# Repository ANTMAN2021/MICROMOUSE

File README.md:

# MICROMOUSE
As a Team Robotics projects, this is a stm32 based micromouse.
There are two pcbs, one based on stm32f103c8t6 and other on stm32f405rgt6.
The assembled bot is on stm32f103 bluepill.
Motor driver used is DRV8833 and sensors are IR sensors.
N20 motors with encoders are used.
Basic running code is given above, shortest path algorithm is in progress.

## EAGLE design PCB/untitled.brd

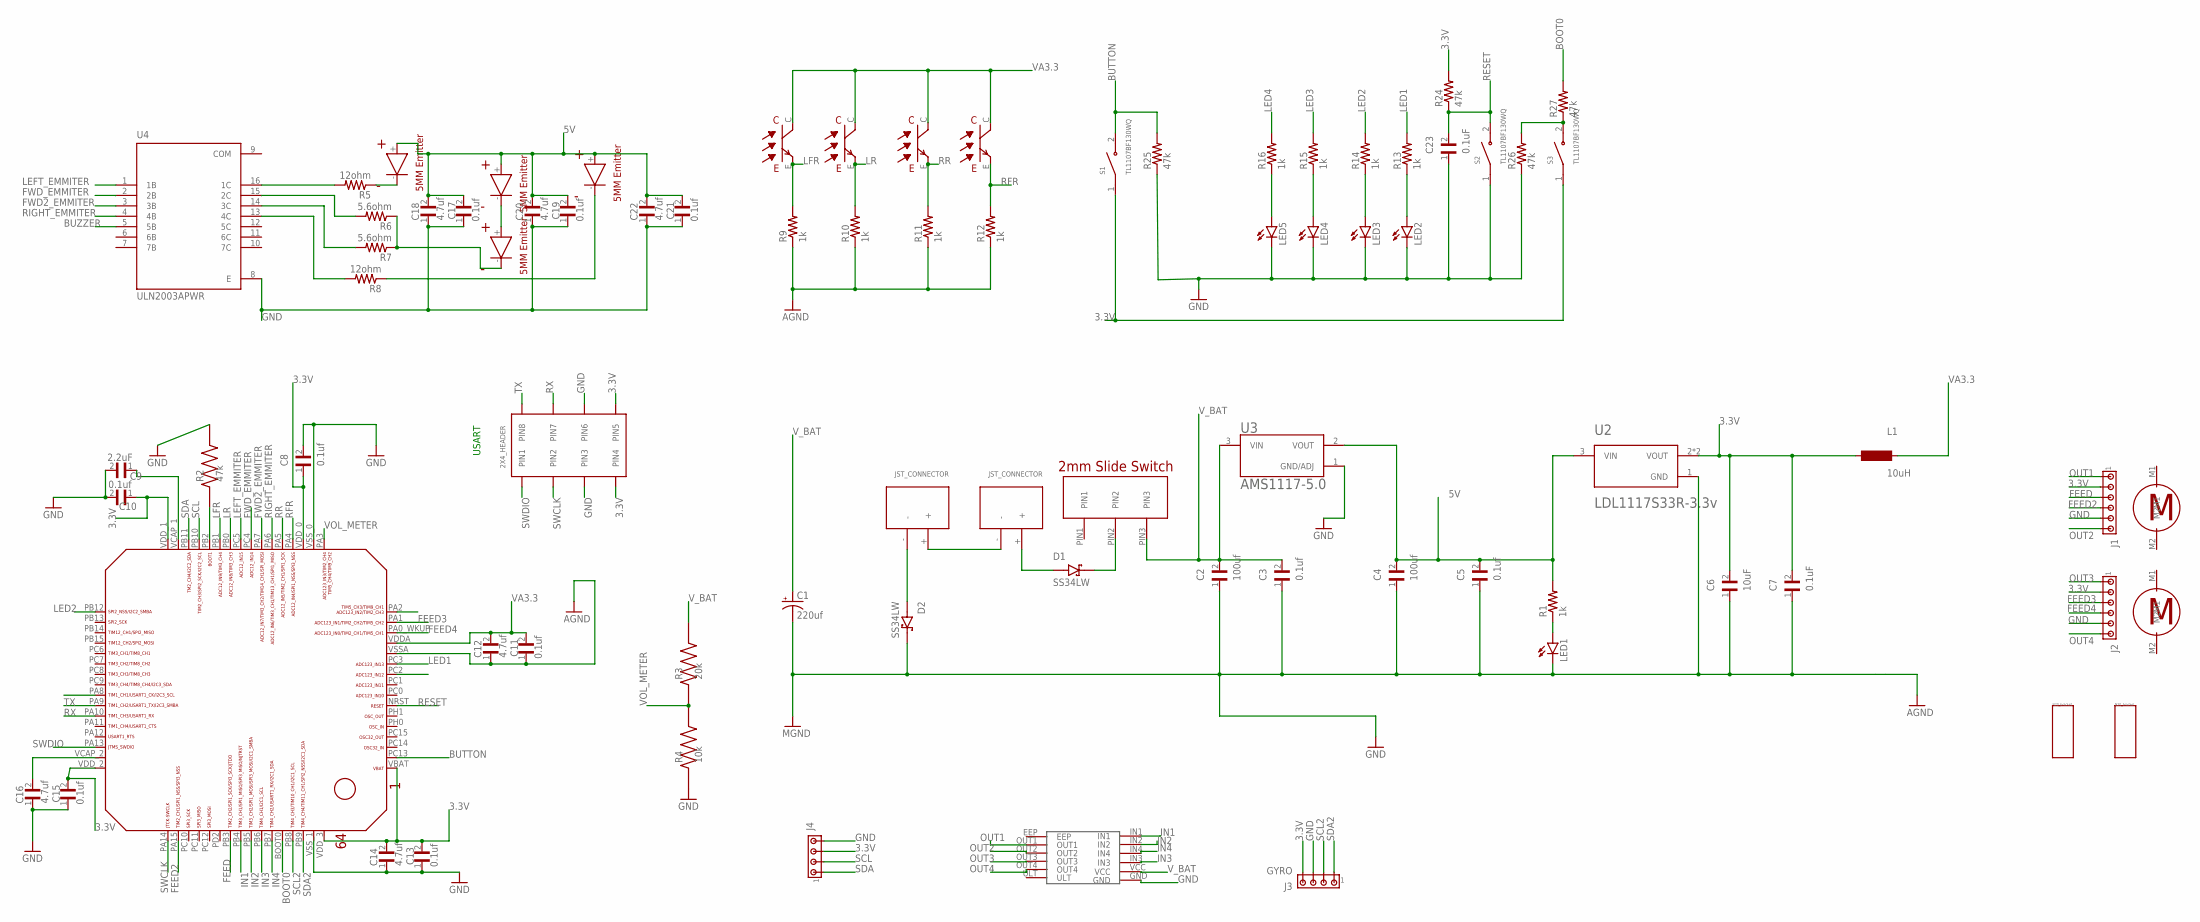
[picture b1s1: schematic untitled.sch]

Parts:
C1: 220uf; EIA3216
C2, C4: 100uf; CAPC0603X35N
C3, C5, C8, C10, C11, C13, C15, C17, C19, C21: 0.1uf; CAPC0603X35N
C6: 10uF; CAPC0603X35N
C7, C23: 0.1uF; CAPC0603X35N
C9: 2.2uF; CAPC0603X35N
C12, C14, C16, C18, C20, C22: 4.7uf; CAPC0603X35N
D1, D2: SS34LW; SODFL3718X102N
EMMI1: EMITTER
J1, J2: MTA06-100; 10X06MTA
J3: GYRO; 10X04MTA
J4: MTA04-100; 10X04MTA
L1: 10uH; MS42
LED1, LED2, LED3, LED4, LED5: LEDCHIPLED_0805; CHIPLED_0805
R1, R9, R10, R11, R12, R13, R14, R15, R16: 1k; 0603-RES
R2: 47k; RES_ERJU01F3570C
R3: 20k; RES_ERJU01F3570C
R4: 10k; RES_ERJU01F3570C
R5, R8: 12ohm; 0603-RES
R6, R7: 5.6ohm; 0603-RES
R24, R25, R26, R27: 47k; 0603-RES
S1, S2, S3: TL1107BF130WQ; SW_TL1107BF130WQ
STM32F405RGT6: STM32F405/415_LQFP64
U2: LDL1117S33R-3.3v; SOT230P700X180-4N
U3: AMS1117-5.0; SOT229P700X180-4N
U4: ULN2003APWR; SOP65P640X120-16N
U$1, U$4: N20_BRACKET; BRACKER
U$2, U$3: MOTOR_N20
U$5, U$6: JST_CONNECTOR_FEMALE
U$8: 2MMS_SLIDE_SWITCH
U$10: 2X3_HEADER
U$11: DRV8833
U$12, U$16, U$17, U$18: RECEIVER
U$13, U$14, U$15: EMITTER

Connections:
3.3V: C6.2, C7.2, C8.1, C10.1, C13.2, C14.2, C15.2, J1.2, J2.2, J3.4, J4.3, L1.1, R24.2, S1.1, S3.1, STM32F405RGT6.VBAT, STM32F405RGT6.VDD_0, STM32F405RGT6.VDD_1, STM32F405RGT6.VDD_2, STM32F405RGT6.VDD_3, U2.2 (VOUT), U2.4 (VOUT), U$10.PIN4, U$10.PIN5
5V: C4.2, C5.2, C17.2, C18.2, C19.2, C20.2, C21.2, C22.2, EMMI1.+, R1.2, U2.3 (VIN), U3.2 (VOUT), U$13.+, U$15.+
BOOT0: R27.2, STM32F405RGT6.BOOT0
BUTTON: R25.2, S1.2, STM32F405RGT6.PC13
BUZZER: U4.5 (5B)
COM: U4.9 (COM)
FEED: J1.3, STM32F405RGT6.PB3
FEED2: J1.4, STM32F405RGT6.PA15
FEED3: J2.3, STM32F405RGT6.PA1
FEED4: J2.4, STM32F405RGT6.PA0_WKUP (PA0_AKUP)
FWD2_EMMITER: STM32F405RGT6.PA7, U4.3 (3B)
FWD_EMMITER: STM32F405RGT6.PC4, U4.2 (2B)
GND: C1.C (-), C2.1, C3.1, C4.1, C5.1, C6.1, C7.1, C8.2, C9.2, C10.2, C11.1, C12.1, C13.1, C14.1, C15.1, C16.1, C17.1, C18.1, C19.1, C20.1, C21.1, C22.1, C23.1, D2.C (K), J1.5, J2.5, J3.3, J4.4, LED1.C, LED2.C, LED3.C, LED4.C, LED5.C, R2.2, R4.1, R9.1, R10.1, R11.1, R12.1, R25.1, R26.1, S2.1, STM32F405RGT6.VSSA, STM32F405RGT6.VSS_0, STM32F405RGT6.VSS_1, U2.1 (GND), U3.1 (GND/ADJ), U4.8 (E), U$10.PIN3, U$10.PIN6, U$11.GND
IN1: STM32F405RGT6.PB4, U$11.IN1
IN2: STM32F405RGT6.PB5, U$11.IN2
IN3: STM32F405RGT6.PB6, U$11.IN3
IN4: STM32F405RGT6.PB7, U$11.IN4
LED1: R13.2, STM32F405RGT6.PC3
LED2: R14.2, STM32F405RGT6.PB12
LED3: R15.2, STM32F405RGT6.PC2
LED4: R16.2, STM32F405RGT6.PA8
LEFT_EMMITER: STM32F405RGT6.PC5, U4.1 (1B)
LFR: R9.2, STM32F405RGT6.PB1, U$18.E
LR: R10.2, STM32F405RGT6.PB0, U$17.E
unnamed: U$13.-, U$14.+
unnamed: U$5.+, U$6.-
unnamed: R2.1, STM32F405RGT6.PB2
unnamed: D1.C (K), U$8.PIN2
unnamed: R7.2, U4.14 (3C)
unnamed: C9.1, STM32F405RGT6.VCAP_1
unnamed: LED1.A, R1.1
unnamed: C16.2, STM32F405RGT6.VCAP_2
unnamed: LED2.A, R13.1
unnamed: D1.A, U$6.+
unnamed: EMMI1.-, R5.1
unnamed: R5.2, U4.16 (1C)
unnamed: D2.A, U$5.-
unnamed: LED3.A, R14.1
unnamed: R6.2, U4.15 (2C)
unnamed: R6.1, R7.1, U$14.-
unnamed: R8.2, U4.13 (4C)
unnamed: R8.1, U$15.-
unnamed: LED4.A, R15.1
unnamed: R26.2, R27.1, S3.2
unnamed: LED5.A, R16.1
OUT1: J1.1, U$11.OUT1
OUT2: J1.6, U$11.OUT2
OUT3: J2.1, U$11.OUT3
OUT4: J2.6, U$11.OUT4
RESET: C23.2, R24.1, S2.2, STM32F405RGT6.NRST
RFR: R12.2, STM32F405RGT6.PA4, U$12.E
RIGHT_EMMITER: STM32F405RGT6.PA6, U4.4 (4B)
RR: R11.2, STM32F405RGT6.PA5, U$16.E
RX: STM32F405RGT6.PA10, U$10.PIN7
SCL: J4.2, STM32F405RGT6.PB10
SCL2: J3.2, STM32F405RGT6.PB8
SDA: J4.1, STM32F405RGT6.PB11
SDA2: J3.1, STM32F405RGT6.PB9
SWCLK: STM32F405RGT6.PA14, U$10.PIN2
SWDIO: STM32F405RGT6.PA13, U$10.PIN1
TX: STM32F405RGT6.PA9, U$10.PIN8
VA3.3: C11.2, C12.2, L1.2, STM32F405RGT6.VDDA, U$12.C, U$16.C, U$17.C, U$18.C
VOL_METER: R3.1, R4.2, STM32F405RGT6.PA3
V_BAT: C1.A (+), C2.2, C3.2, R3.2, U3.3 (VIN), U$8.PIN3, U$11.VCC

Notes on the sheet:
USART

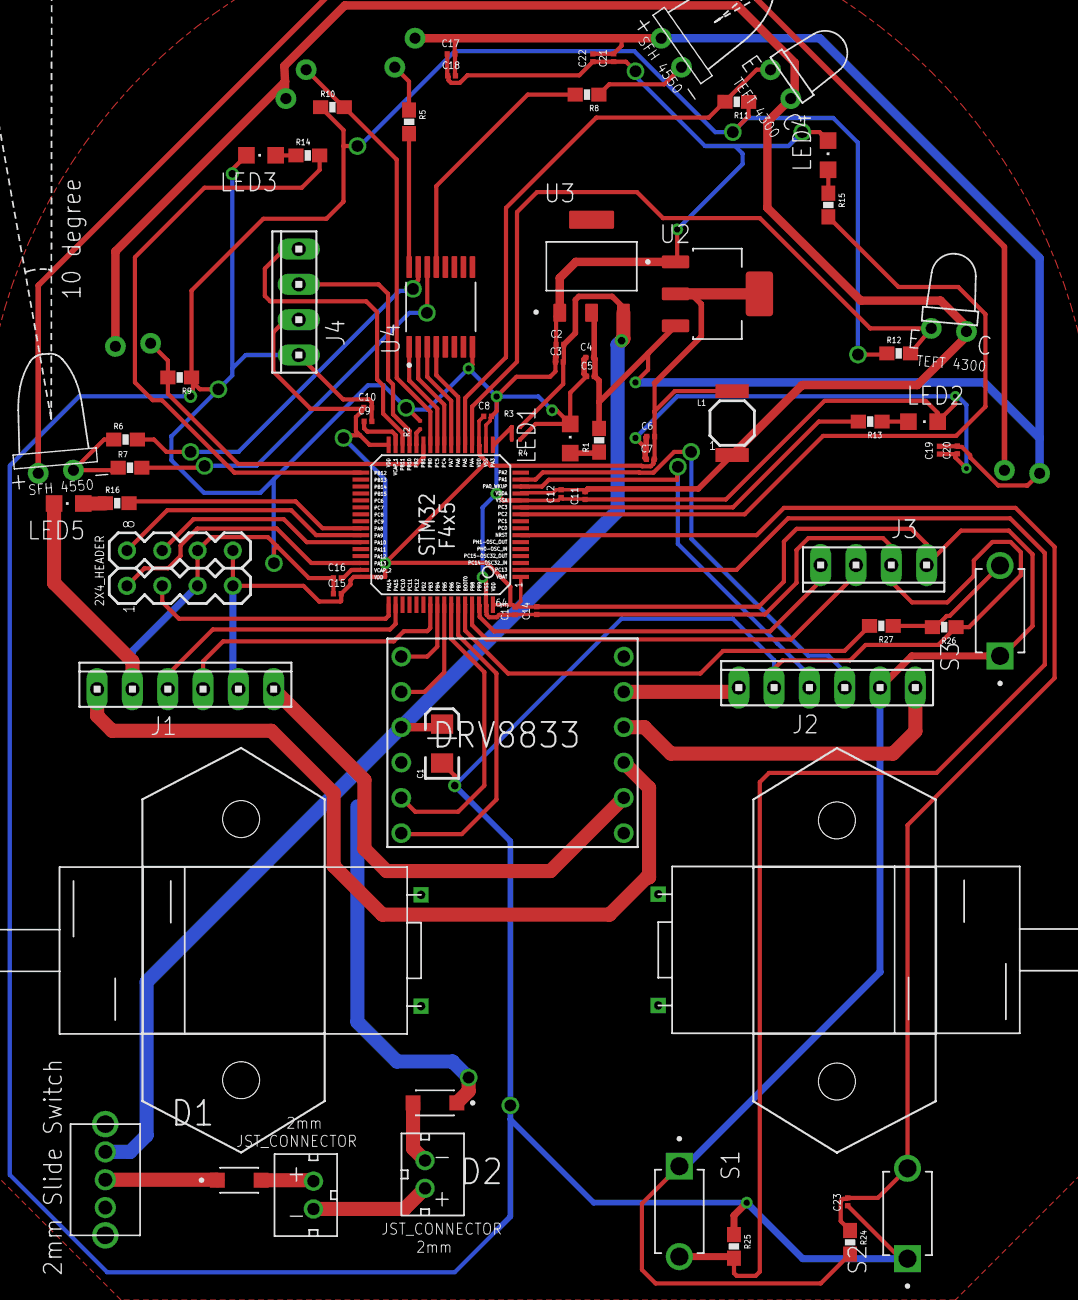
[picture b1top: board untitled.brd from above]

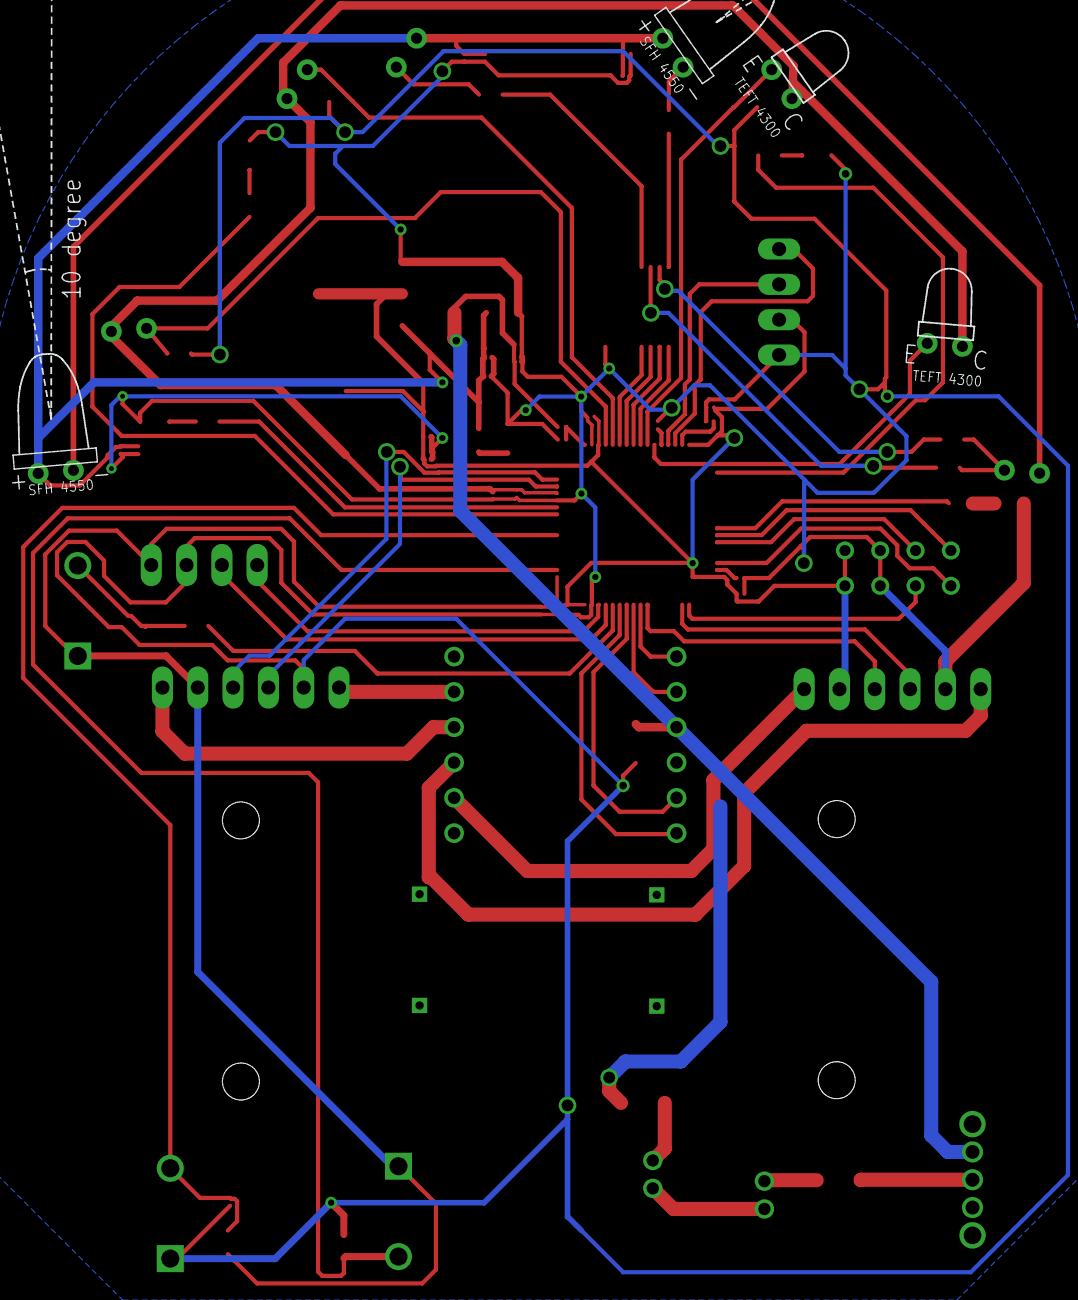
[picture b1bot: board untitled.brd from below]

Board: 2 copper layers, 79 parts (4 on the bottom side), 62 nets.

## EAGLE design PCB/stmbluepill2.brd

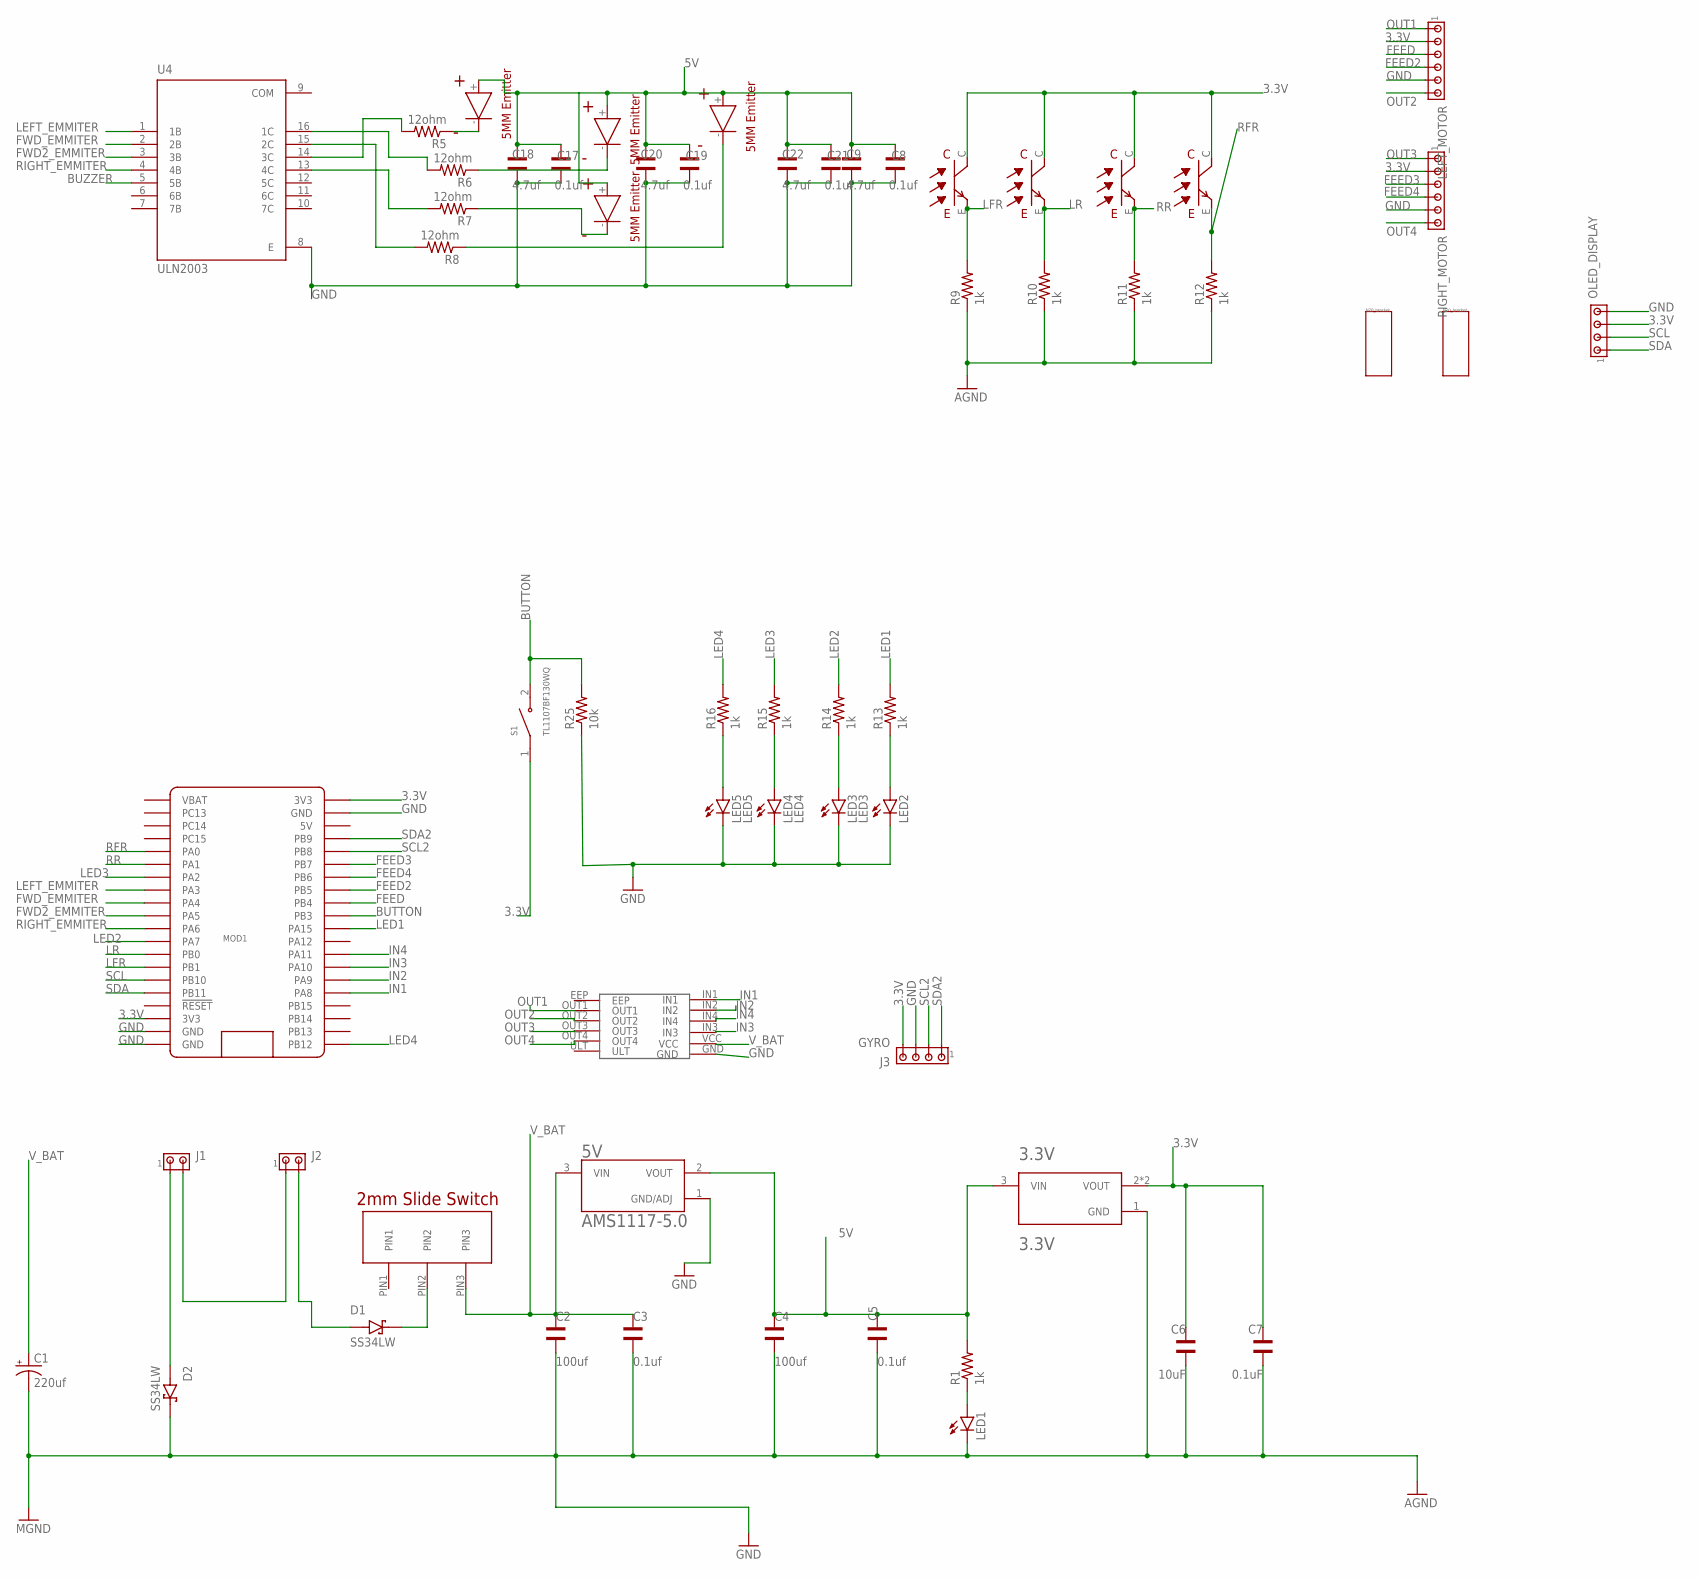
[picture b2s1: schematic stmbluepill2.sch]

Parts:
3.3V: 3.3V; SOT230P700X180-4N
5V: AMS1117-5.0; SOT229P700X180-4N
C1: 220uf; EIA3216
C2, C4: 100uf; WCAP-CSGP_885012206026
C3, C5, C8, C17, C19, C21: 0.1uf; WCAP-CSGP_885012206026
C6: 10uF; WCAP-CSGP_885012206026
C7: 0.1uF; WCAP-CSGP_885012206026
C9, C18, C20, C22: 4.7uf; WCAP-CSGP_885012206026
D1, D2: SS34LW; SODFL3718X102N
EMMI1: EMITTER
J1, J2: MTA02-100; 10X02MTA
J3: GYRO; 10X04MTA
LED1, LED2: LEDCHIPLED_0805; CHIPLED_0805
LED3: LED3; CHIPLED_0805
LED4: LED4; CHIPLED_0805
LED5: LED5; CHIPLED_0805
LEFT_MOTOR: MTA06-100; 10X06MTA
MOD1: BLUE_PILLADVANCED; BLUE_PILL_ADV
OLED_DISPLAY: MTA04-100; 10X04MTA
R1, R9, R10, R11, R12, R13, R14, R15, R16: 1k; 0603-RES
R5, R6, R7, R8: 12ohm; 0603-RES
R25: 10k; 0603-RES
RIGHT_MOTOR: MTA06-100; 10X06MTA
S1: TL1107BF130WQ; SW_TL1107BF130WQ
U4: ULN2003; SOP65P640X120-16N
U$1, U$4: N20_BRACKET; BRACKER
U$8: 2MMS_SLIDE_SWITCH
U$11: DRV8833
U$12, U$16, U$17, U$18: RECEIVER
U$13, U$14, U$15: EMITTER

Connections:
3.3V: 3.3V.2 (VOUT), 3.3V.4 (VOUT), C6.2, C7.2, J3.4, LEFT_MOTOR.2, MOD1.P$20 (3V3), MOD1.P$23 (3V3), OLED_DISPLAY.3, RIGHT_MOTOR.2, S1.1, U$12.C, U$16.C, U$17.C, U$18.C
5V: 3.3V.3 (VIN), 5V.2 (VOUT), C4.2, C5.2, C8.2, C9.2, C17.2, C18.2, C19.2, C20.2, C21.2, C22.2, EMMI1.+, R1.2, U$13.+, U$14.+, U$15.+
BUTTON: MOD1.P$11 (PB3), R25.2, S1.2
BUZZER: U4.5 (5B)
COM: U4.9 (COM)
FEED: LEFT_MOTOR.3, MOD1.P$12 (PB4)
FEED2: LEFT_MOTOR.4, MOD1.P$13 (PB5)
FEED3: MOD1.P$15 (PB7), RIGHT_MOTOR.3
FEED4: MOD1.P$14 (PB6), RIGHT_MOTOR.4
FWD2_EMMITER: MOD1.P$31 (PA5), U4.3 (3B)
FWD_EMMITER: MOD1.P$32 (PA4), U4.2 (2B)
GND: 3.3V.1 (GND), 5V.1 (GND/ADJ), C1.C (-), C2.1, C3.1, C4.1, C5.1, C6.1, C7.1, C8.1, C9.1, C17.1, C18.1, C19.1, C20.1, C21.1, C22.1, D2.C (K), J3.3, LED1.C, LED2.C, LED3.C, LED4.C, LED5.C, LEFT_MOTOR.5, MOD1.P$19 (GND), MOD1.P$21 (GND), MOD1.P$22 (GND), OLED_DISPLAY.4, R9.1, R10.1, R11.1, R12.1, R25.1, RIGHT_MOTOR.5, U4.8 (E), U$11.GND
IN1: MOD1.P$5 (PA8), U$11.IN1
IN2: MOD1.P$6 (PA9), U$11.IN2
IN3: MOD1.P$7 (PA10), U$11.IN3
IN4: MOD1.P$8 (PA11), U$11.IN4
LED1: MOD1.P$10 (PA15), R13.2
LED2: MOD1.P$29 (PA7), R14.2
LED3: MOD1.P$34 (PA2), R15.2
LED4: MOD1.P$1 (PB12), R16.2
LEFT_EMMITER: MOD1.P$33 (PA3), U4.1 (1B)
LFR: MOD1.P$27 (PB1), R9.2, U$18.E
LR: MOD1.P$28 (PB0), R10.2, U$17.E
unnamed: R6.1, U$13.-
unnamed: J1.2, J2.1
unnamed: D1.C (K), U$8.PIN2
unnamed: R7.2, U4.13 (4C)
unnamed: R5.2, U4.14 (3C)
unnamed: LED1.A, R1.1
unnamed: R6.2, U4.16 (1C)
unnamed: LED2.A, R13.1
unnamed: D1.A, J2.2
unnamed: EMMI1.-, R5.1
unnamed: D2.A, J1.1
unnamed: LED3.A, R14.1
unnamed: R7.1, U$14.-
unnamed: R8.2, U4.15 (2C)
unnamed: R8.1, U$15.-
unnamed: LED4.A, R15.1
unnamed: LED5.A, R16.1
OUT1: LEFT_MOTOR.1, U$11.OUT1
OUT2: LEFT_MOTOR.6, U$11.OUT2
OUT3: RIGHT_MOTOR.1, U$11.OUT3
OUT4: RIGHT_MOTOR.6, U$11.OUT4
RFR: MOD1.P$36 (PA0), R12.2, U$12.E
RIGHT_EMMITER: MOD1.P$30 (PA6), U4.4 (4B)
RR: MOD1.P$35 (PA1), R11.2, U$16.E
SCL: MOD1.P$26 (PB10), OLED_DISPLAY.2
SCL2: J3.2, MOD1.P$16 (PB8)
SDA: MOD1.P$25 (PB11), OLED_DISPLAY.1
SDA2: J3.1, MOD1.P$17 (PB9)
V_BAT: 5V.3 (VIN), C1.A (+), C2.2, C3.2, U$8.PIN3, U$11.VCC

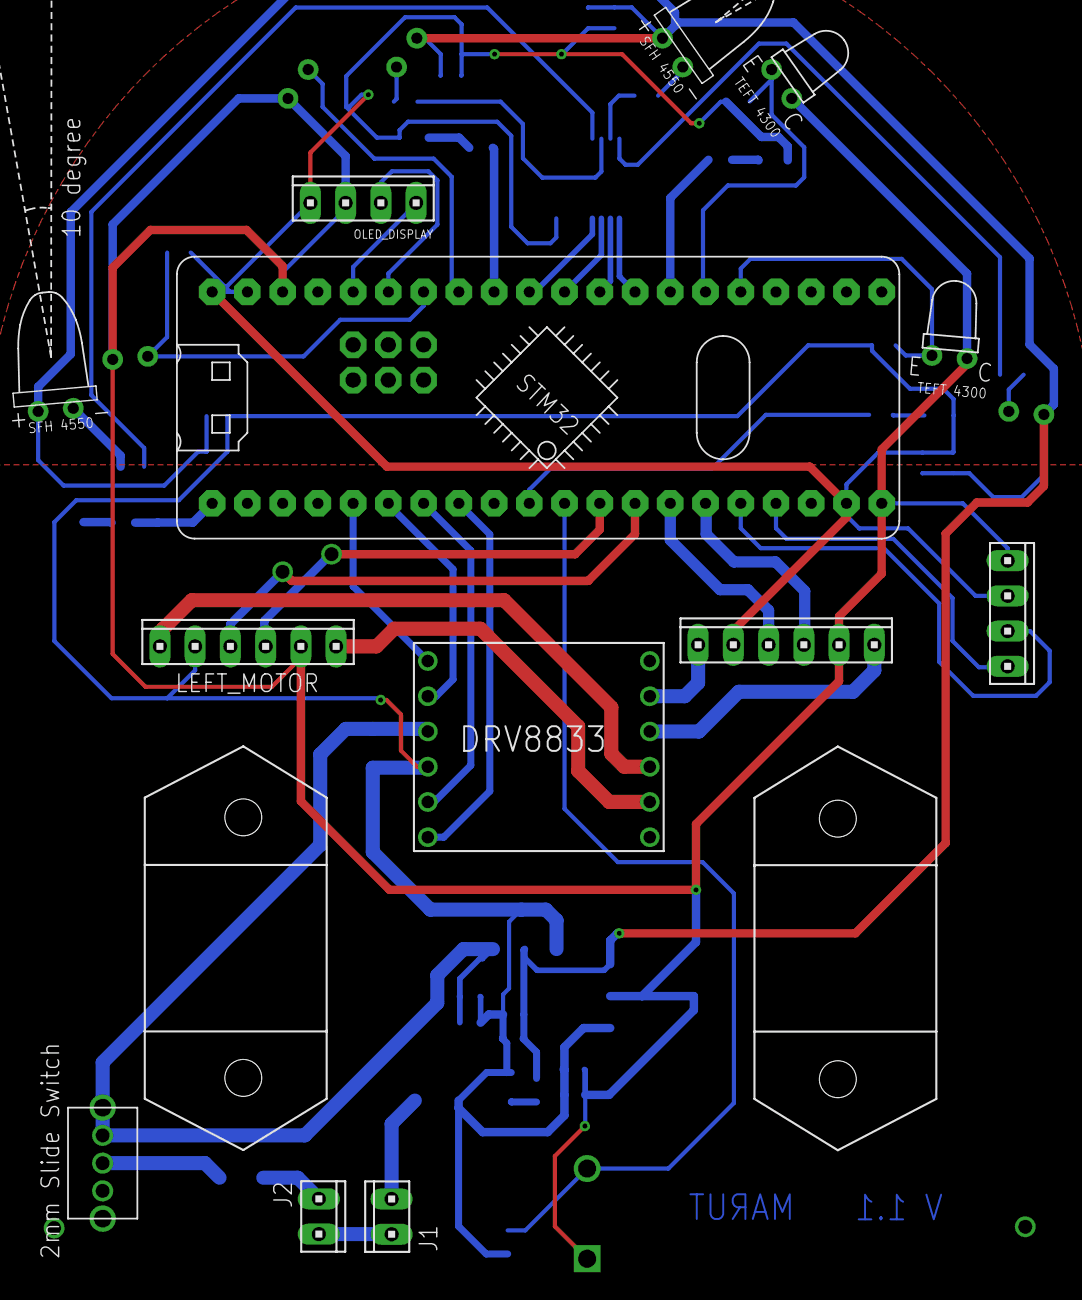
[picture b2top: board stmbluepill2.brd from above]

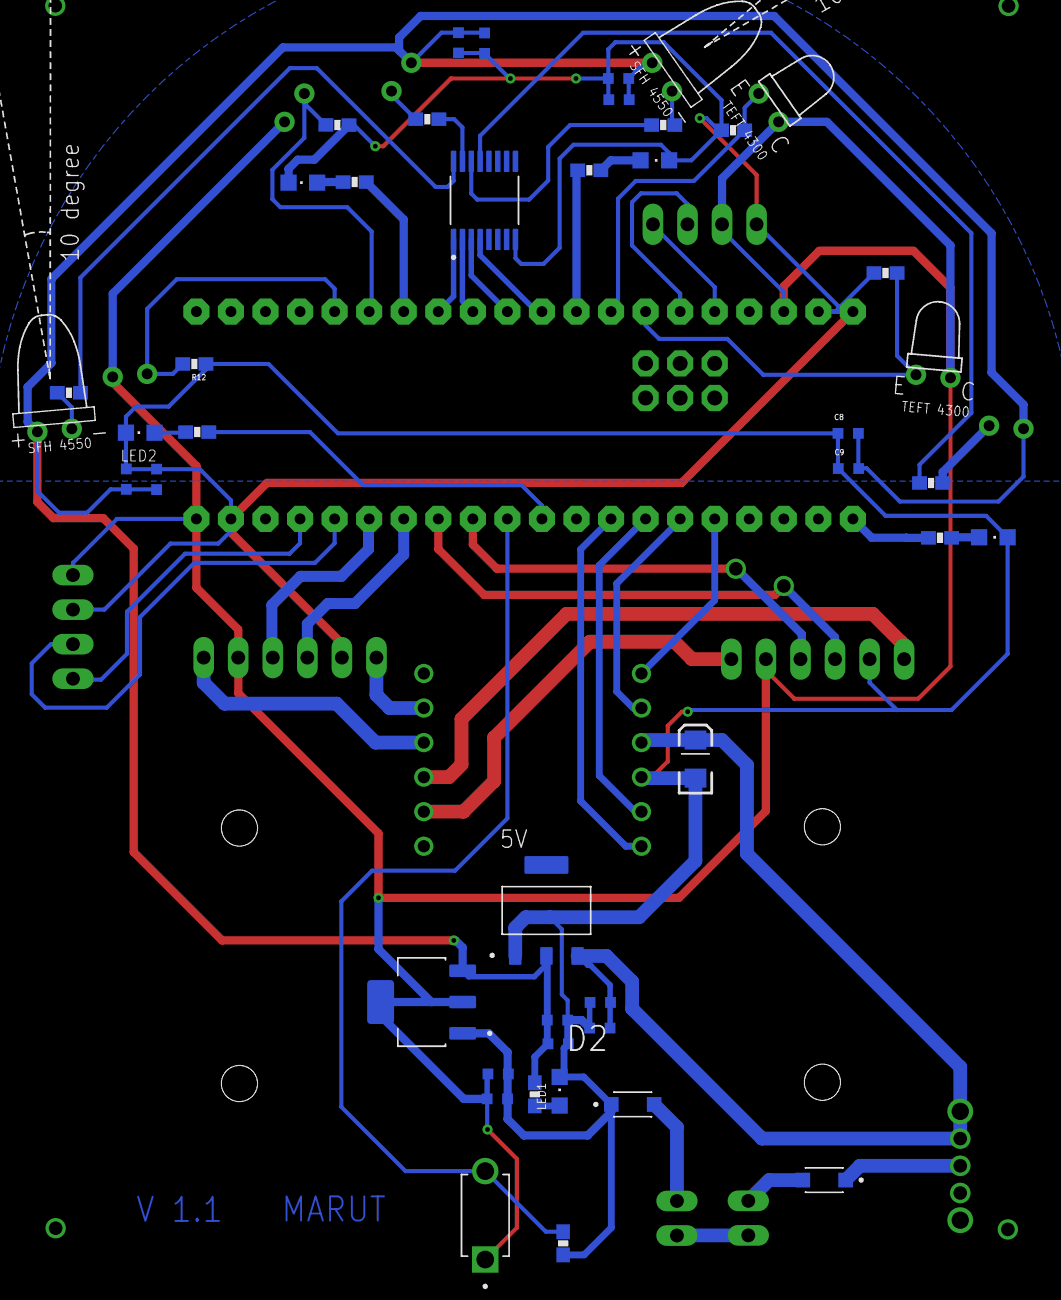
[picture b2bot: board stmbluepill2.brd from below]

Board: 2 copper layers, 59 parts (44 on the bottom side), 50 nets.

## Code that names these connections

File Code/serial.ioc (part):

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Mcu.Name=STM32F103C(8-B)Tx
Mcu.Package=LQFP48
Mcu.UserName=STM32F103C8Tx
PA0-WKUP.Signal=ADCx_IN0
PA1.Signal=ADCx_IN1
PA10.Signal=S_TIM1_CH3
PA11.Signal=S_TIM1_CH4
PA13.Mode=Serial_Wire
PA13.Signal=SYS_JTMS-SWDIO
PA14.Mode=Serial_Wire
PA14.Signal=SYS_JTCK-SWCLK
PA2.GPIOParameters=GPIO_Label
PA2.GPIO_Label=led3
PA2.Signal=GPIO_Output
PA3.GPIOParameters=GPIO_Label
PA3.GPIO_Label=l_emi
PA3.Signal=GPIO_Output
PA4.GPIOParameters=GPIO_Label
PA4.GPIO_Label=f_emi
PA4.Signal=GPIO_Output
PA5.GPIOParameters=GPIO_Label
PA5.GPIO_Label=f2_emi
PA5.Signal=GPIO_Output
PA6.GPIOParameters=GPIO_Label
PA6.GPIO_Label=r_emi
PA6.Signal=GPIO_Output
PA7.GPIOParameters=GPIO_Label
PA7.GPIO_Label=led2
PA7.Signal=GPIO_Output
PA8.Signal=S_TIM1_CH1
PA9.Signal=S_TIM1_CH2
PB0.Signal=ADCx_IN8
PB1.Signal=ADCx_IN9
PB10.Mode=Asynchronous
PB10.Signal=USART3_TX
PB11.Mode=Asynchronous
PB11.Signal=USART3_RX
PB12.GPIOParameters=GPIO_Label
PB12.GPIO_Label=led4
PB12.Signal=GPIO_Output
PB7.GPIOParameters=GPIO_Label
PB7.GPIO_Label=led1
PB7.Signal=GPIO_Output
PD0-OSC_IN.Mode=HSE-External-Oscillator
PD0-OSC_IN.Signal=RCC_OSC_IN
PD1-OSC_OUT.Mode=HSE-External-Oscillator
PD1-OSC_OUT.Signal=RCC_OSC_OUT
RCC.SYSCLKFreq_VALUE=72000000
RCC.SYSCLKSource=RCC_SYSCLKSOURCE_PLLCLK
board=custom

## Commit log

2024-08-04 Create cd
2024-08-04 Create main
2024-08-04 Rename main to main.h

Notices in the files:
parts and their libraries:
SparkFun: Licensing: CC v3.0 Share-Alike You are welcome to use this library for commercial purposes.
